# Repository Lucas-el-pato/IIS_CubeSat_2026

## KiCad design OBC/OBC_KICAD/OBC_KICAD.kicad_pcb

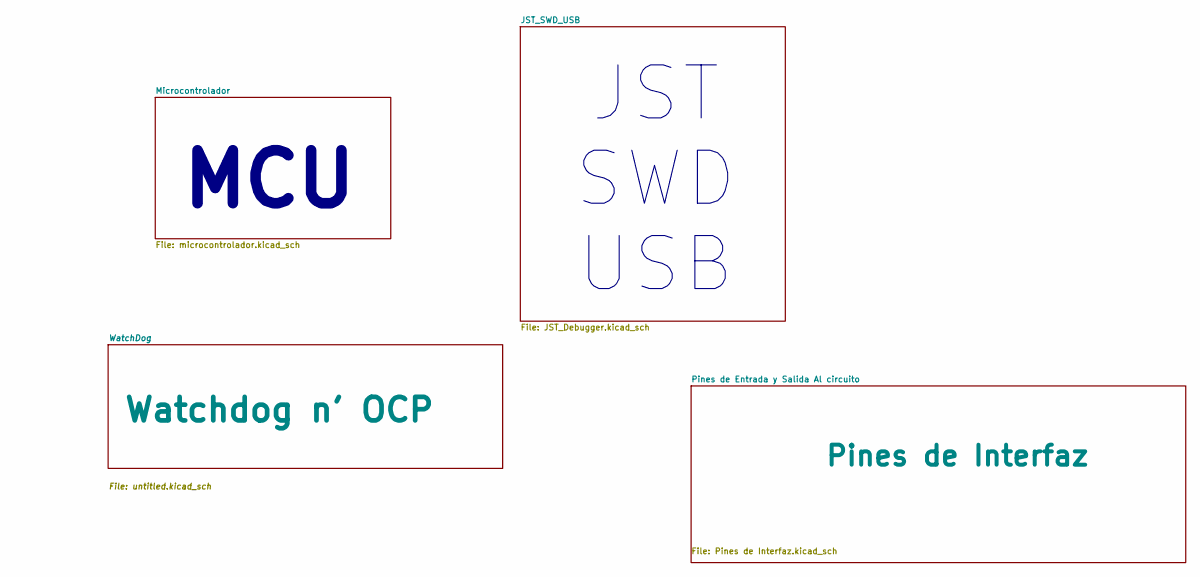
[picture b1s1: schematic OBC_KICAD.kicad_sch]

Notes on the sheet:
JST SWD USB
MCU

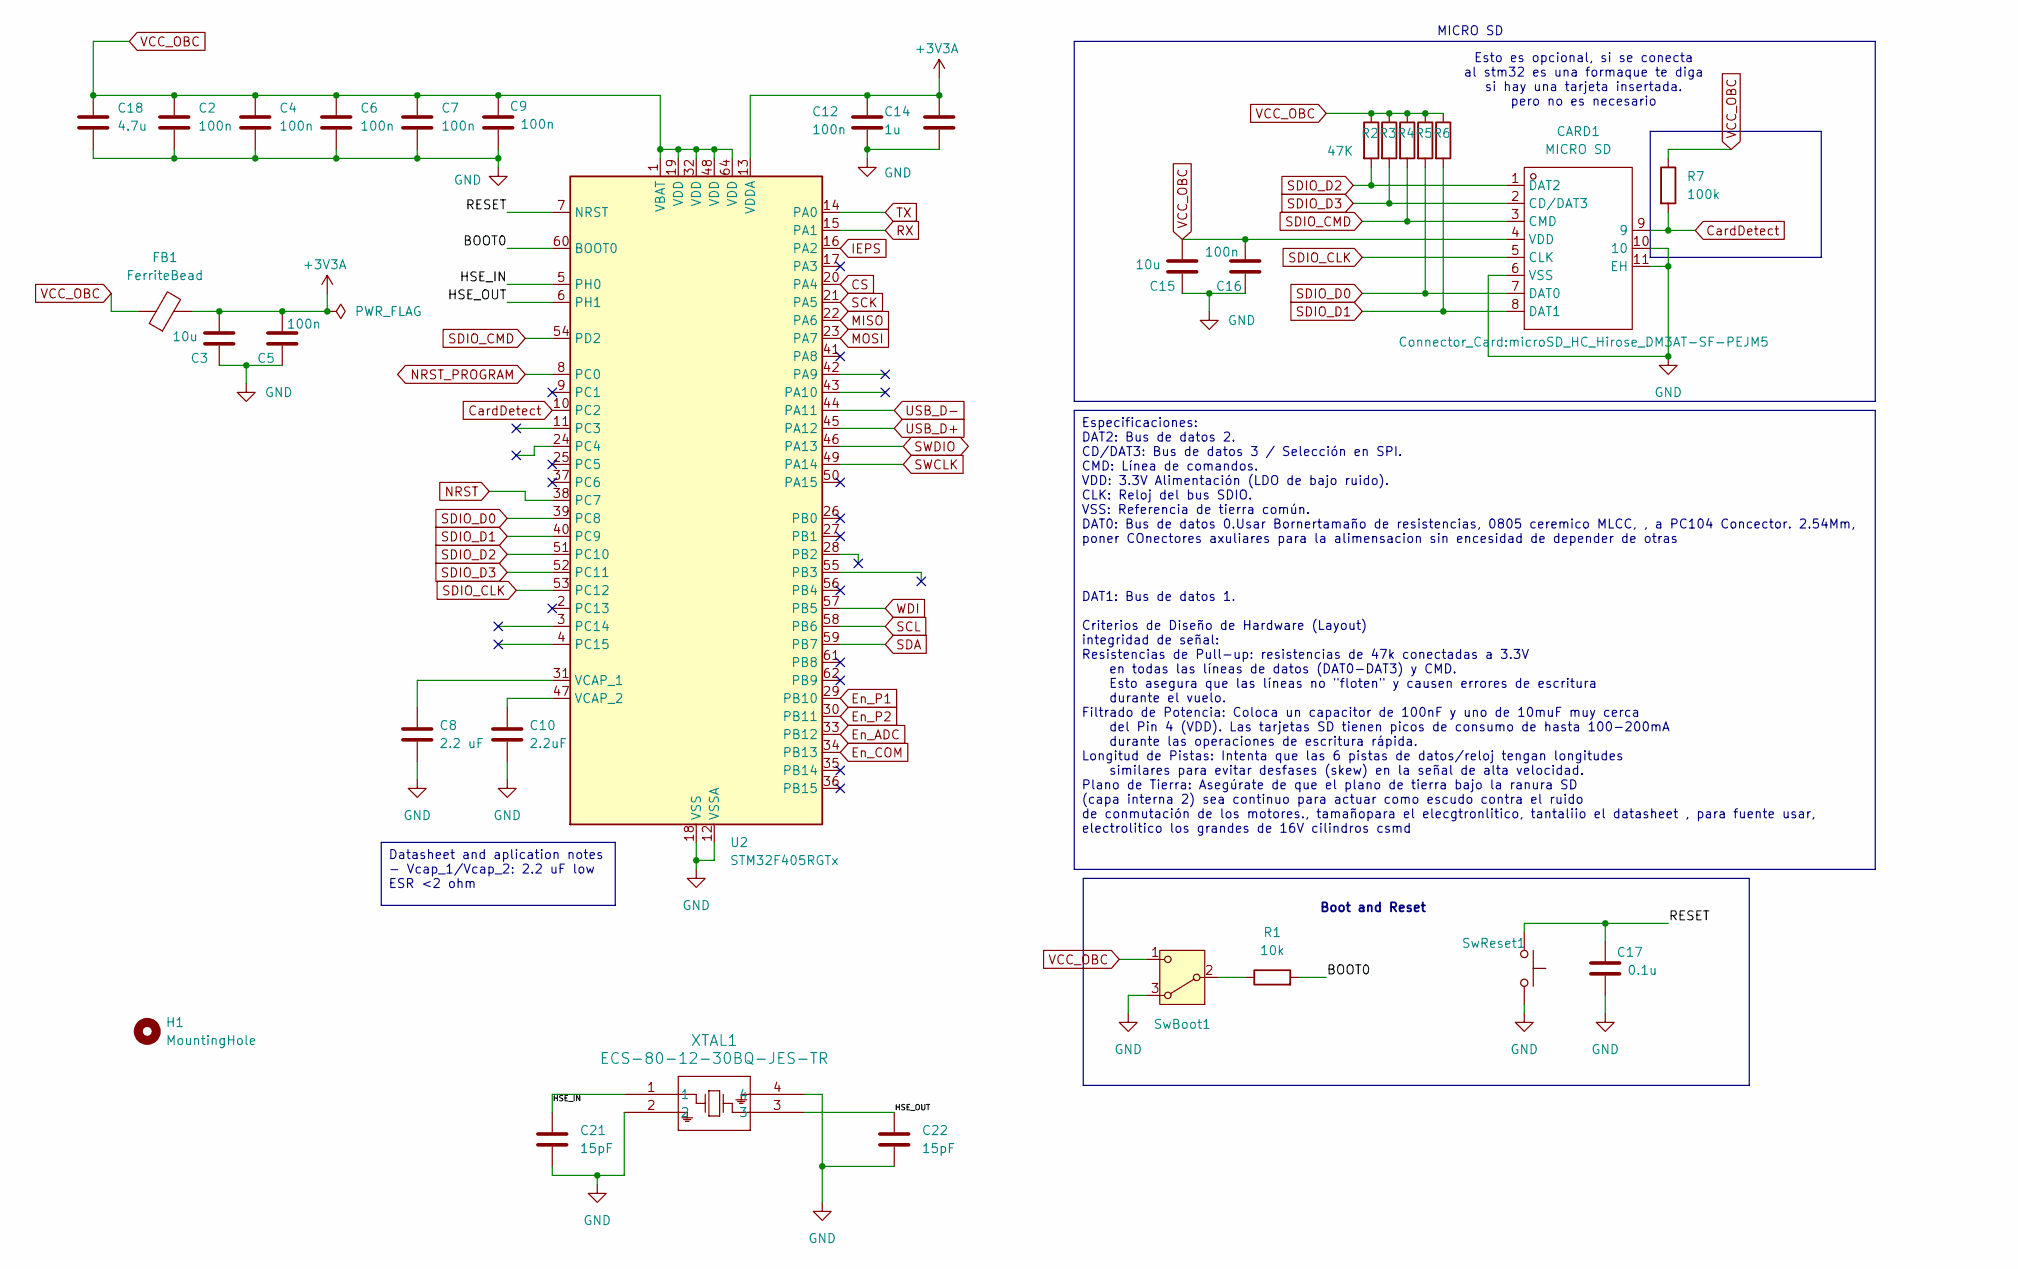
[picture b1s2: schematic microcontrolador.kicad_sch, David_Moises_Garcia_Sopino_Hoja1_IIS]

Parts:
C2, C4, C5, C6, C7, C9, C12, C16: 100n; C_0805_2012Metric_Pad1.18x1.45mm_HandSolder
C3, C15: 10u; C_0805_2012Metric_Pad1.18x1.45mm_HandSolder
C8: 2.2 uF; C_0805_2012Metric_Pad1.18x1.45mm_HandSolder
C10: 2.2uF; C_0805_2012Metric_Pad1.18x1.45mm_HandSolder
C14: 1u; C_0805_2012Metric_Pad1.18x1.45mm_HandSolder
C17: 0.1u; C_0805_2012Metric_Pad1.18x1.45mm_HandSolder
C18: 4.7u; C_0805_2012Metric_Pad1.18x1.45mm_HandSolder
C21, C22: 15pF; C_0805_2012Metric_Pad1.18x1.45mm_HandSolder
CARD1: MICRO SD; microSD_HC_Hirose_DM3AT-SF-PEJM5; LCSC Part Name 自弹式 MicroSD卡(TF卡) 卡座
FB1: FerriteBead; L_Walsin_WLFM252009x
H1: MountingHole; MountingHole_3.2mm_M3_Pad_Via
R1: 10k; R_0805_2012Metric_Pad1.20x1.40mm_HandSolder
R2, R3, R4, R5, R6: 47K; R_0805_2012Metric_Pad1.20x1.40mm_HandSolder
R7: 100k; R_0805_2012Metric_Pad1.20x1.40mm_HandSolder
SwBoot1: SW_Nidec_CAS-120A1; Nidec_Copal_CAS-120A
SwReset1: SW_Push; SW_Push_1P1T_NO_CK_PTS125Sx43PSMTR
U2: STM32F405RGTx; LQFP-64_10x10mm_P0.5mm
XTAL1: ECS-80-12-30BQ-JES-TR; ECS-80-12_ECS

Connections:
+3V3A: C3.2, C5.2, C12.1, C14.1, FB1.2, U2.13 (VDDA)
/Microcontrolador/BOOT0: R1.2, U2.60 (BOOT0)
/Microcontrolador/HSE_IN: C21.1, U2.5 (PH0), XTAL1.1
/Microcontrolador/HSE_OUT: C22.1, U2.6 (PH1), XTAL1.3
/Microcontrolador/RESET: C17.1, SwReset1.2, U2.7 (NRST)
CS: U2.20 (PA4); also elsewhere on the board
CardDetect: CARD1.9, R7.2, U2.10 (PC2)
En_ADC: U2.33 (PB12); also elsewhere on the board
En_COM: U2.34 (PB13); also elsewhere on the board
En_P1: U2.29 (PB10); also elsewhere on the board
En_P2: U2.30 (PB11); also elsewhere on the board
GND: C2.2, C3.1, C4.2, C5.1, C6.2, C7.2, C8.2, C9.2, C10.2, C12.2, C14.2, C15.1, C16.1, C17.2, C18.2, C21.2, C22.2, CARD1.6 (VSS), CARD1.10, CARD1.11 (EH), SwBoot1.3 (A), SwReset1.1, U2.12 (VSSA), U2.18 (VSS), U2.63 (VSS), XTAL1.2, XTAL1.4; also elsewhere on the board
IEPS: U2.16 (PA2); also elsewhere on the board
MISO: U2.22 (PA6); also elsewhere on the board
MOSI: U2.23 (PA7); also elsewhere on the board
NRST: U2.38 (PC7); also elsewhere on the board
NRST_PROGRAM: U2.8 (PC0); also elsewhere on the board
unnamed: R1.1, SwBoot1.2 (B)
unnamed: C8.1, U2.31 (VCAP_1)
unnamed: C10.1, U2.47 (VCAP_2)
RX: U2.15 (PA1); also elsewhere on the board
SCK: U2.21 (PA5); also elsewhere on the board
SCL: U2.58 (PB6); also elsewhere on the board
SDA: U2.59 (PB7); also elsewhere on the board
SDIO_CLK: CARD1.5 (CLK), U2.53 (PC12)
SDIO_CMD: CARD1.3 (CMD), R4.2, U2.54 (PD2)
SDIO_D0: CARD1.7 (DAT0), R5.2, U2.39 (PC8)
SDIO_D1: CARD1.8 (DAT1), R6.2, U2.40 (PC9)
SDIO_D2: CARD1.1 (DAT2), R2.2, U2.51 (PC10)
SDIO_D3: CARD1.2 (CD/DAT3), R3.2, U2.52 (PC11)
SWCLK: U2.49 (PA14); also elsewhere on the board
SWDIO: U2.46 (PA13); also elsewhere on the board
TX: U2.14 (PA0); also elsewhere on the board
USB_D+: U2.45 (PA12); also elsewhere on the board
USB_D-: U2.44 (PA11); also elsewhere on the board
VCC_OBC: C2.1, C4.1, C6.1, C7.1, C9.1, C15.2, C16.2, C18.1, CARD1.4 (VDD), FB1.1, R2.1, R3.1, R4.1, R5.1, R6.1, R7.1, SwBoot1.1 (C), U2.1 (VBAT), U2.19 (VDD), U2.32 (VDD), U2.48 (VDD), U2.64 (VDD); also elsewhere on the board
WDI: U2.57 (PB5); also elsewhere on the board

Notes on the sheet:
Esto es opcional, si se conecta al stm32 es una formaque te diga si hay una tarjeta insertada. pero no es necesario
Boot and Reset
MICRO SD
Datasheet and aplication notes - Vcap_1/Vcap_2: 2.2 uF low ESR <2 ohm
Especificaciones: DAT2: Bus de datos 2. CD/DAT3: Bus de datos 3 / Selección en SPI. CMD: Línea de comandos. VDD: 3.3V Alimentación (LDO de bajo ruido). CLK: Reloj del bus SDIO. VSS: Referencia de tierra común. DAT0: Bus de datos 0.Usar Bornertamaño de resistencias, 0805 ceremico MLCC, , a PC104 Con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

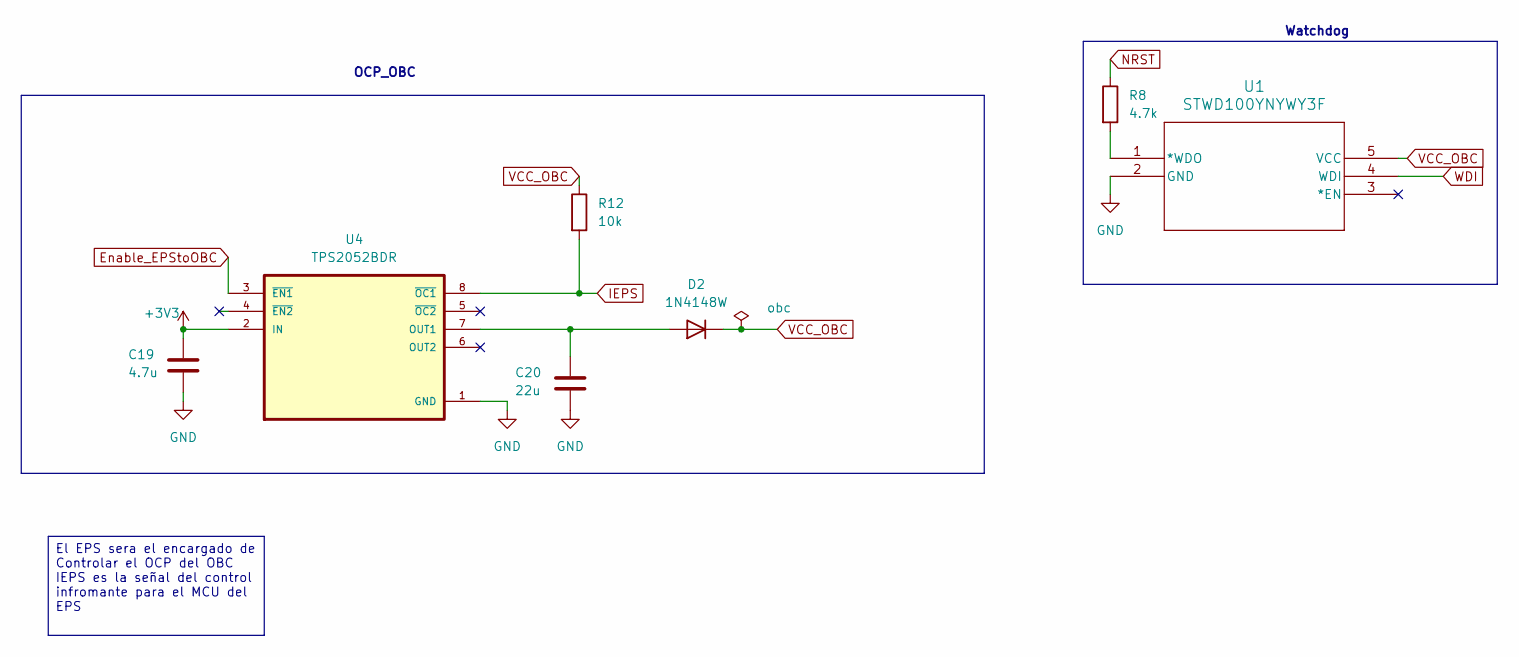
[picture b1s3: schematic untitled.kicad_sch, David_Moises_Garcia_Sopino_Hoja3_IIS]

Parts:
C19: 4.7u; C_0805_2012Metric_Pad1.18x1.45mm_HandSolder
C20: 22u; C_0805_2012Metric_Pad1.18x1.45mm_HandSolder
D2: 1N4148W; D_SOD-123
R8: 4.7k; R_0805_2012Metric_Pad1.20x1.40mm_HandSolder
R12: 10k; R_0805_2012Metric_Pad1.20x1.40mm_HandSolder
U1: STWD100YNYWY3F; SOP95P280X145-5N
U4: TPS2052BDR; SOIC127P599X175-8N

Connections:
+3V3: C19.1, U4.2 (IN); also elsewhere on the board
Enable_EPStoOBC: U4.3 (~EN1); also elsewhere on the board
GND: C19.2, C20.2, U1.2 (GND), U4.1 (GND); also elsewhere on the board
IEPS: R12.2, U4.8 (~OC1); also elsewhere on the board
NRST: R8.1; also elsewhere on the board
unnamed: C20.1, D2.2 (A), U4.7 (OUT1)
unnamed: R8.2, U1.1 (*WDO)
VCC_OBC: D2.1 (K), R12.1, U1.5 (VCC); also elsewhere on the board
WDI: U1.4 (WDI); also elsewhere on the board

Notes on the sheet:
OCP_OBC
Watchdog
El EPS sera el encargado de Controlar el OCP del OBC IEPS es la señal del control infromante para el MCU del EPS

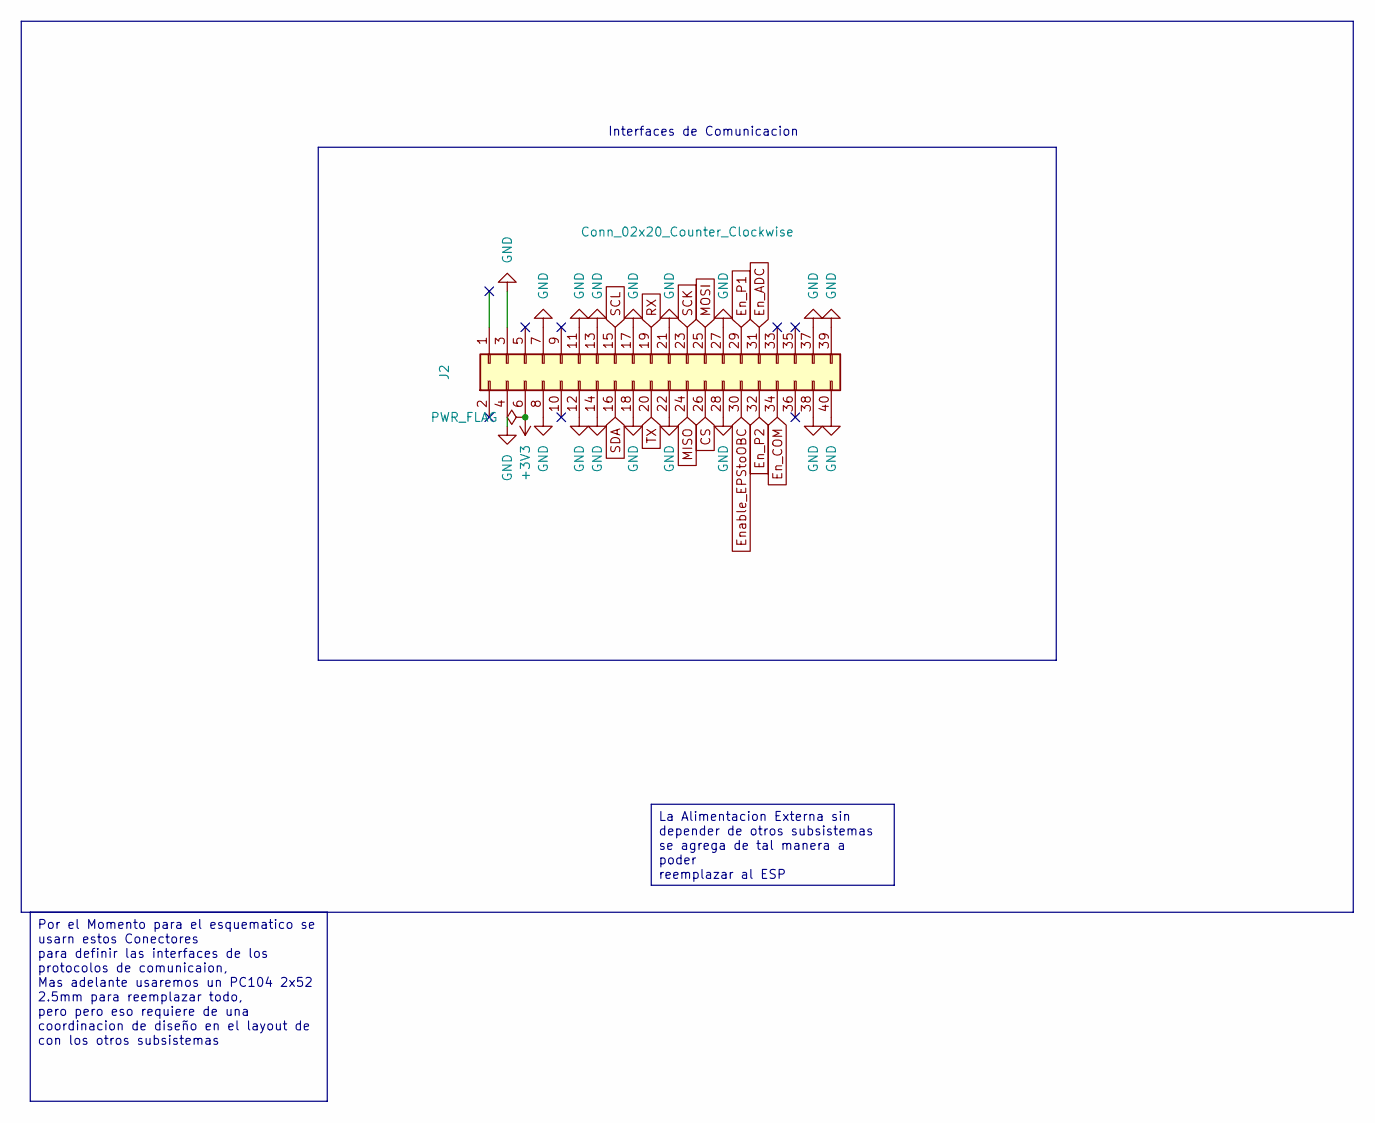
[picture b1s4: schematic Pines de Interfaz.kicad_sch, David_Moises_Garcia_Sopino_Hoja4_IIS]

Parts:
J2: Conn_02x20_Counter_Clockwise; PinSocket_2x20_P2.54mm_Vertical

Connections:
+3V3: J2.6; also elsewhere on the board
CS: J2.26; also elsewhere on the board
En_ADC: J2.31; also elsewhere on the board
En_COM: J2.34; also elsewhere on the board
En_P1: J2.29; also elsewhere on the board
En_P2: J2.32; also elsewhere on the board
Enable_EPStoOBC: J2.30; also elsewhere on the board
GND: J2.3, J2.4, J2.7, J2.8, J2.11, J2.12, J2.13, J2.14, J2.17, J2.18, J2.21, J2.22, J2.27, J2.28, J2.37 (Pin_38), J2.38, J2.39 (Pin_39}), J2.40; also elsewhere on the board
MISO: J2.24; also elsewhere on the board
MOSI: J2.25; also elsewhere on the board
RX: J2.19; also elsewhere on the board
SCK: J2.23; also elsewhere on the board
SCL: J2.15; also elsewhere on the board
SDA: J2.16; also elsewhere on the board
TX: J2.20; also elsewhere on the board

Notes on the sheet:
Interfaces de Comunicacion
Por el Momento para el esquematico se usarn estos Conectores para definir las interfaces de los protocolos de comunicaion, Mas adelante usaremos un PC104 2x52 2.5mm para reemplazar todo, pero pero eso requiere de una coordinacion de diseño en el layout de con los otros subsistemas
La Alimentacion Externa sin depender de otros subsistemas se agrega de tal manera a poder reemplazar al ESP

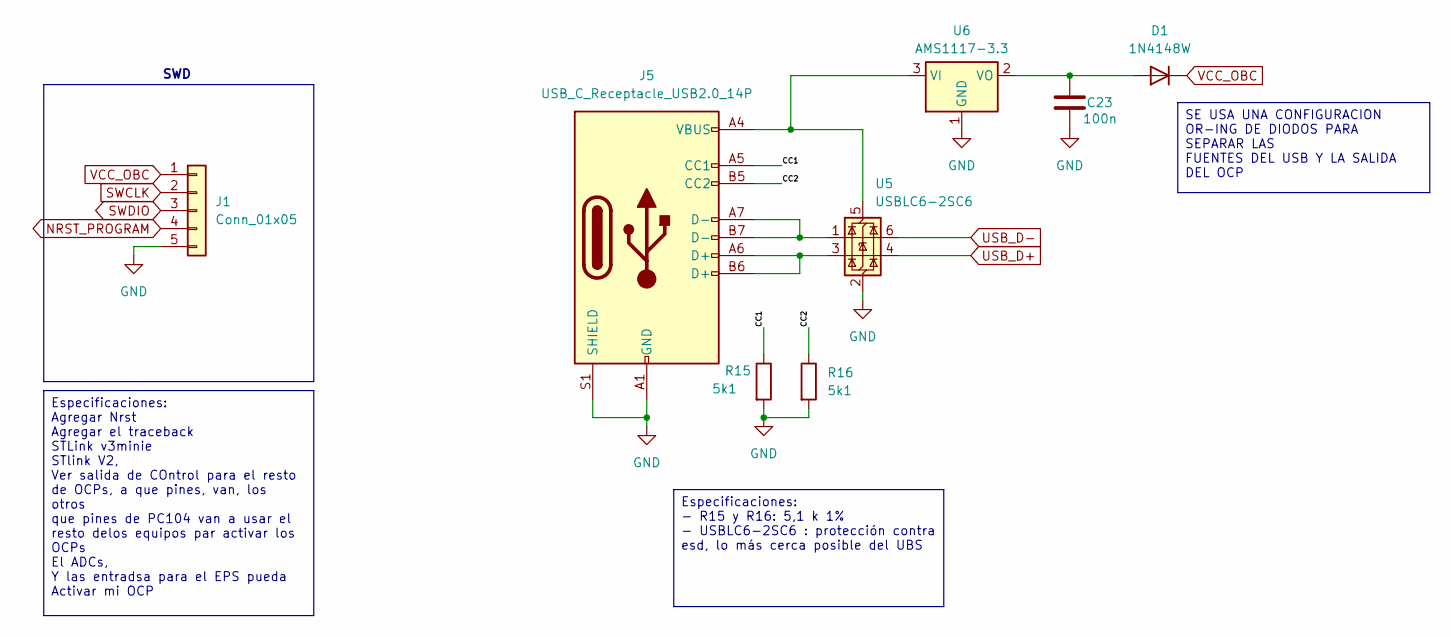
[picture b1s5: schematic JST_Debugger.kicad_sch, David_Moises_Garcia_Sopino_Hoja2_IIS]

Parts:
C23: 100n; C_0805_2012Metric_Pad1.18x1.45mm_HandSolder
D1: 1N4148W; D_SOD-123
J1: Conn_01x05; PinSocket_1x05_P2.54mm_Vertical_SMD_Pin1Left
J5: USB_C_Receptacle_USB2.0_14P; USB_C_Receptacle_GCT_USB4110
R15, R16: 5k1; R_0805_2012Metric_Pad1.20x1.40mm_HandSolder
U5: USBLC6-2SC6; SOT-23-6
U6: AMS1117-3.3; SOT-223-3_TabPin2

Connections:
/JST_SWD_USB/CC1: J5.A5 (CC1), R15.1
/JST_SWD_USB/CC2: J5.B5 (CC2), R16.1
GND: C23.2, J1.5, J5.A1 (GND), J5.A12 (GND), J5.B1 (GND), J5.B12 (GND), J5.S1 (SHIELD), R15.2, R16.2, U5.2 (GND), U6.1 (GND); also elsewhere on the board
NRST_PROGRAM: J1.4; also elsewhere on the board
unnamed: C23.1, D1.2 (A), U6.2 (VO)
unnamed: J5.A6 (D+), J5.B6 (D+), U5.3 (I/O2)
unnamed: J5.A7 (D-), J5.B7 (D-), U5.1 (I/O1)
unnamed: J5.A4 (VBUS), J5.A9 (VBUS), J5.B4 (VBUS), J5.B9 (VBUS), U5.5 (VBUS), U6.3 (VI)
SWCLK: J1.2; also elsewhere on the board
SWDIO: J1.3; also elsewhere on the board
USB_D+: U5.4 (I/O2); also elsewhere on the board
USB_D-: U5.6 (I/O1); also elsewhere on the board
VCC_OBC: D1.1 (K), J1.1; also elsewhere on the board

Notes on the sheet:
SWD
Especificaciones: Agregar Nrst Agregar el traceback STLink v3minie STlink V2, Ver salida de COntrol para el resto de OCPs, a que pines, van, los otros que pines de PC104 van a usar el resto delos equipos par activar los OCPs El ADCs, Y las entradsa para el EPS pueda Activar mi OCP
SE USA UNA CONFIGURACION OR-ING DE DIODOS PARA SEPARAR LAS FUENTES DEL USB Y LA SALIDA DEL OCP
Especificaciones: - R15 y R16: 5,1 k 1% - USBLC6-2SC6 : protección contra esd, lo más cerca posible del UBS

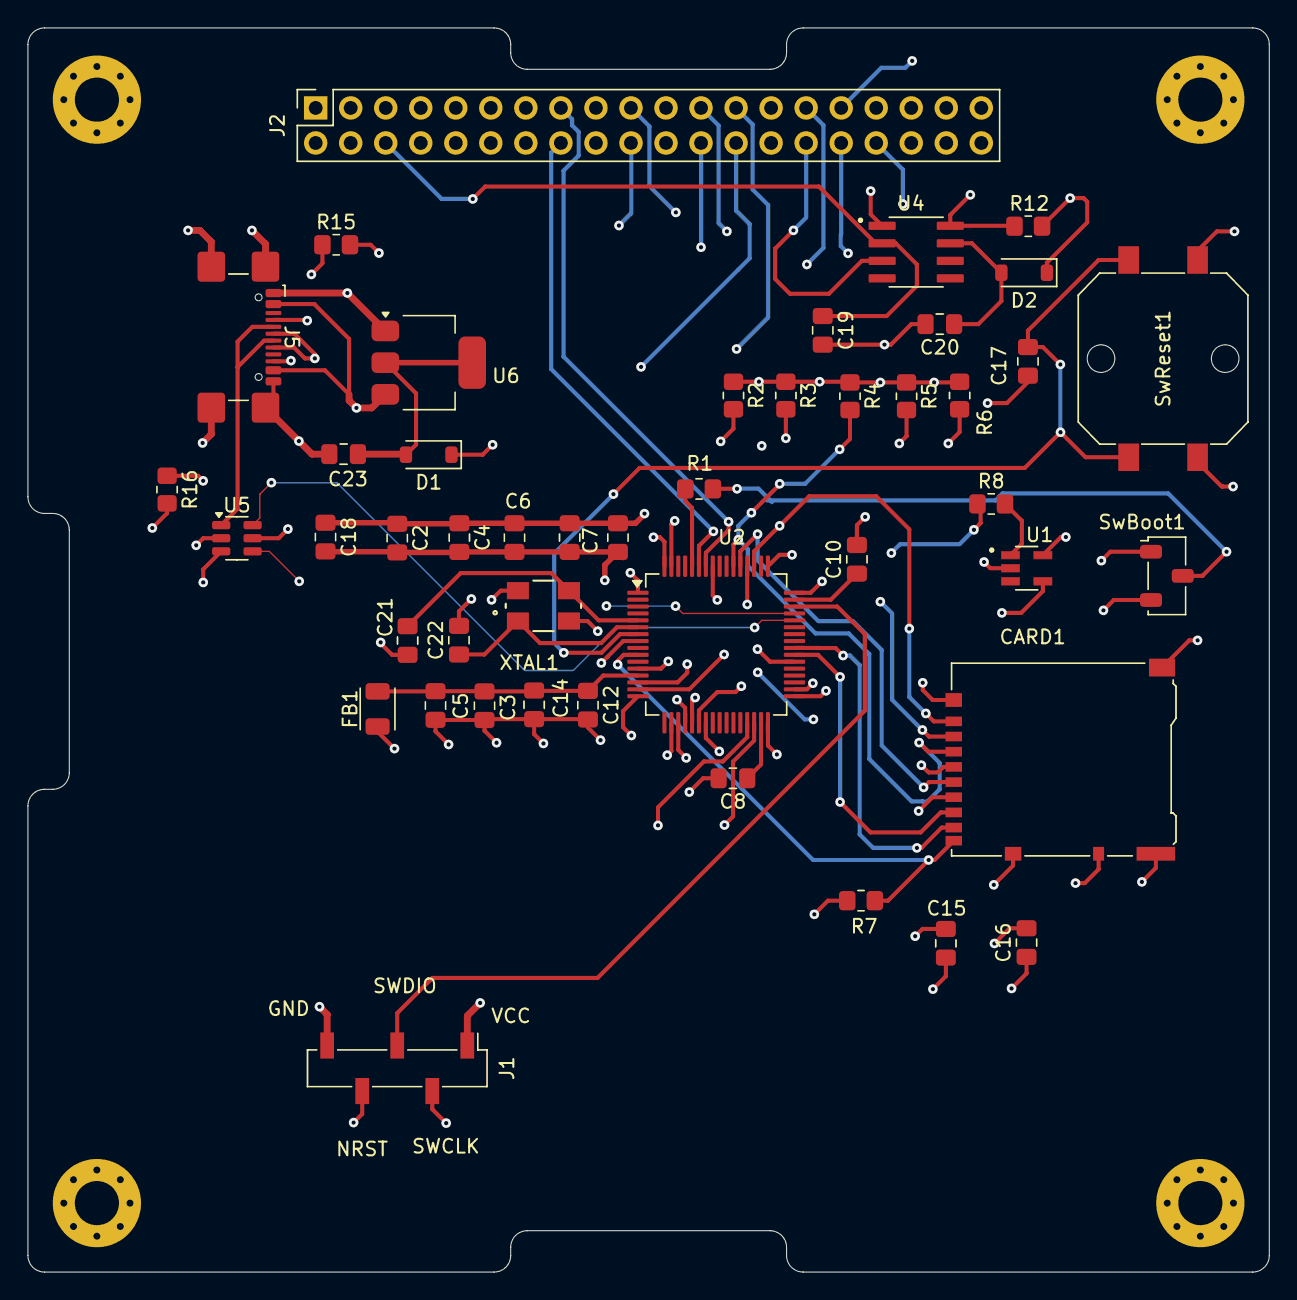
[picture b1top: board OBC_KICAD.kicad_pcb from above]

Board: 4 copper layers, 90.0 x 90.2 mm, 50 parts (0 on the bottom side), 47 nets.

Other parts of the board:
H2, H3, H4: MountingHole; MountingHole_3.2mm_M3_Pad_Via

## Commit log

2026-03-07 Read Me .txt
    Read Me .txt Para todos los sub sistemas
2026-03-07 Added Diagram.drawio
2026-03-07 Initial OBC Kicad
    Kicad del OBC con el STM32 y el jst para SWD y el USB
2026-03-09 footprints y datasheets
2026-03-30 Agregar OCP TPS2052BDR y Watchdog STWD100
    Agregue un OCP y un WatchDOg ,todo en la HOja con NOmbre Wtachdog.
2026-05-04 Cirtcuito Completo
    Circuito Completo
